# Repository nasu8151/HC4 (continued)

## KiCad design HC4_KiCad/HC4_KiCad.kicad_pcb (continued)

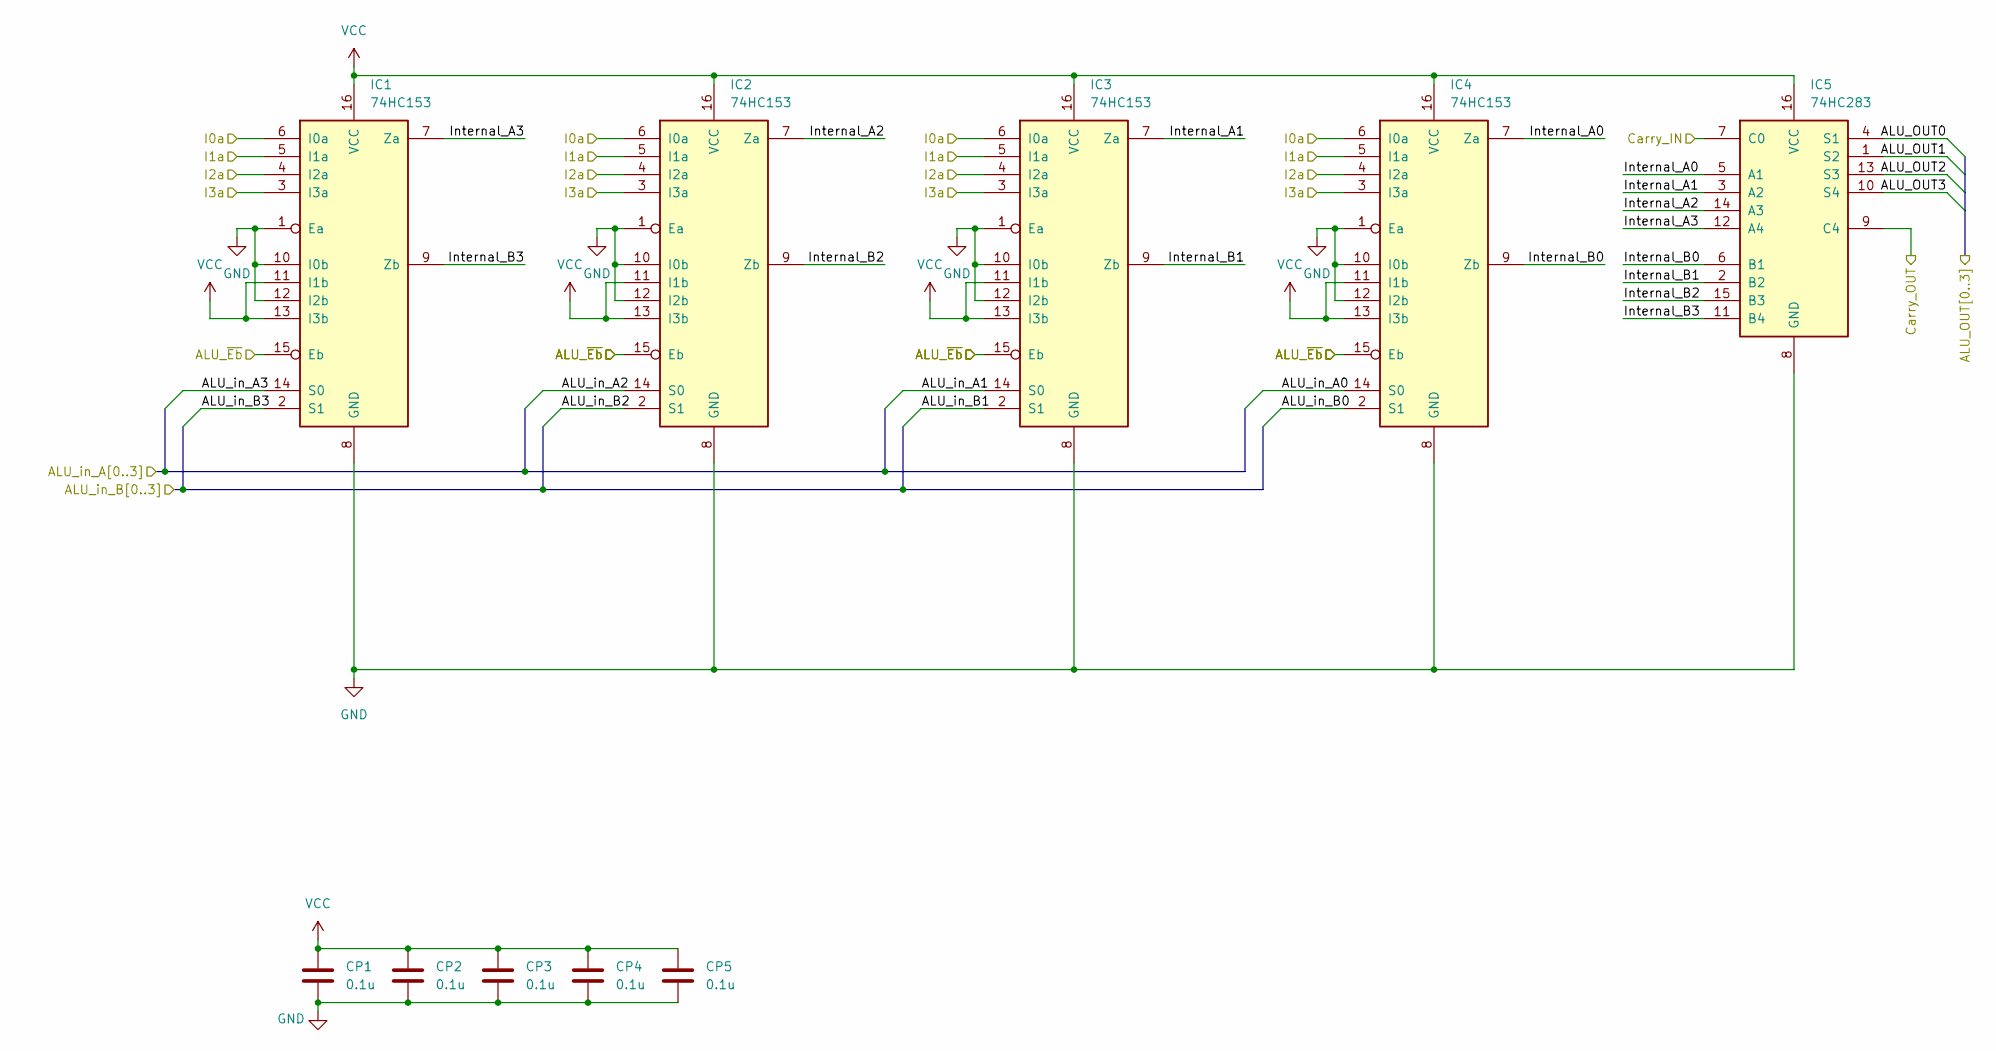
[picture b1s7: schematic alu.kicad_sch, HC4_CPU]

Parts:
CP1, CP2, CP3, CP4, CP5: 0.1u; C_0603_1608Metric
IC1, IC2, IC3, IC4: 74HC153; DIP-16_W7.62mm
IC5: 74HC283; DIP-16_W7.62mm

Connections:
/ALU/ALU_OUT0: IC5.4 (S1); also elsewhere on the board
/ALU/ALU_OUT1: IC5.1 (S2); also elsewhere on the board
/ALU/ALU_OUT2: IC5.13 (S3); also elsewhere on the board
/ALU/ALU_OUT3: IC5.10 (S4); also elsewhere on the board
/ALU/ALU_in_A0: IC4.14 (S0); also elsewhere on the board
/ALU/ALU_in_A1: IC3.14 (S0); also elsewhere on the board
/ALU/ALU_in_A2: IC2.14 (S0); also elsewhere on the board
/ALU/ALU_in_A3: IC1.14 (S0); also elsewhere on the board
/ALU/ALU_in_B0: IC4.2 (S1); also elsewhere on the board
/ALU/ALU_in_B1: IC3.2 (S1); also elsewhere on the board
/ALU/ALU_in_B2: IC2.2 (S1); also elsewhere on the board
/ALU/ALU_in_B3: IC1.2 (S1); also elsewhere on the board
/ALU/Carry_IN: IC1.6 (I0a), IC2.6 (I0a), IC3.6 (I0a), IC4.6 (I0a), IC5.7 (C0); also elsewhere on the board
/ALU/Carry_OUT: IC5.9 (C4); also elsewhere on the board
/ALU/I1a: IC1.5 (I1a), IC2.5 (I1a), IC3.5 (I1a), IC4.5 (I1a); also elsewhere on the board
/ALU/I2a: IC1.4 (I2a), IC2.4 (I2a), IC3.4 (I2a), IC4.4 (I2a); also elsewhere on the board
/ALU/I3a: IC1.3 (I3a), IC2.3 (I3a), IC3.3 (I3a), IC4.3 (I3a); also elsewhere on the board
/ALU/Internal_A0: IC4.7 (Za), IC5.5 (A1)
/ALU/Internal_A1: IC3.7 (Za), IC5.3 (A2)
/ALU/Internal_A2: IC2.7 (Za), IC5.14 (A3)
/ALU/Internal_A3: IC1.7 (Za), IC5.12 (A4)
/ALU/Internal_B0: IC4.9 (Zb), IC5.6 (B1)
/ALU/Internal_B1: IC3.9 (Zb), IC5.2 (B2)
/ALU/Internal_B2: IC2.9 (Zb), IC5.15 (B3)
/ALU/Internal_B3: IC1.9 (Zb), IC5.11 (B4)
/Instruction Decoder/~Carry_EN: IC1.15 (Eb), IC2.15 (Eb), IC3.15 (Eb), IC4.15 (Eb); also elsewhere on the board
GND: CP1.2, CP2.2, CP3.2, CP4.2, CP5.2, IC1.1 (Ea), IC1.8 (GND), IC1.10 (I0b), IC1.12 (I2b), IC2.1 (Ea), IC2.8 (GND), IC2.10 (I0b), IC2.12 (I2b), IC3.1 (Ea), IC3.8 (GND), IC3.10 (I0b), IC3.12 (I2b), IC4.1 (Ea), IC4.8 (GND), IC4.10 (I0b), IC4.12 (I2b), IC5.8 (GND); also elsewhere on the board
VCC: CP1.1, CP2.1, CP3.1, CP4.1, CP5.1, IC1.11 (I1b), IC1.13 (I3b), IC1.16 (VCC), IC2.11 (I1b), IC2.13 (I3b), IC2.16 (VCC), IC3.11 (I1b), IC3.13 (I3b), IC3.16 (VCC), IC4.11 (I1b), IC4.13 (I3b), IC4.16 (VCC), IC5.16 (VCC); also elsewhere on the board

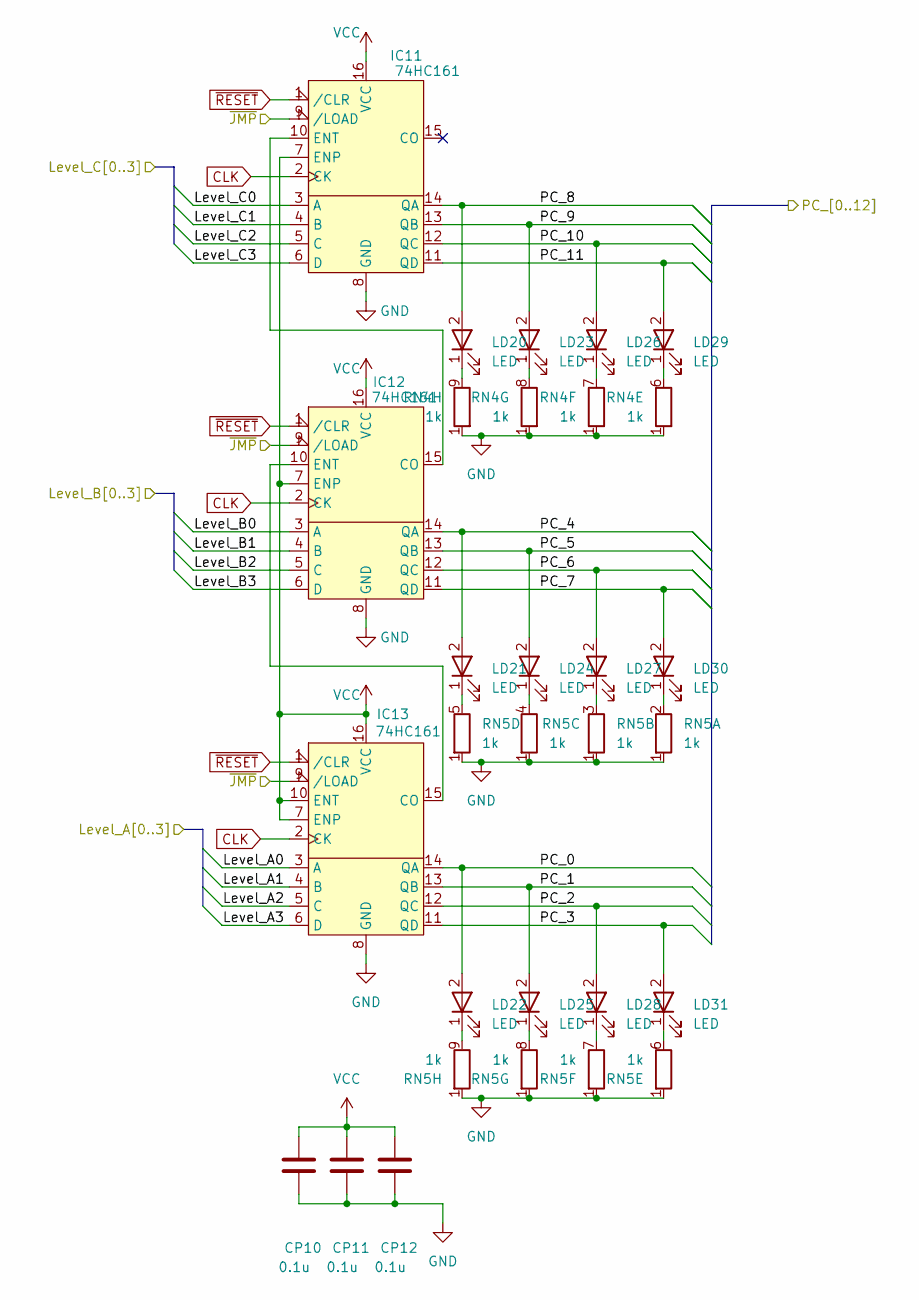
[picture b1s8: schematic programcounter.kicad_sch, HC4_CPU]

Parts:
CP10, CP11, CP12: 0.1u; C_0603_1608Metric
IC11, IC12, IC13: 74HC161; DIP-16_W7.62mm
LD20, LD21, LD22, LD23, LD24, LD25, LD26, LD27, LD28, LD29, LD30, LD31: LED; LED_Rectangular_W5.0mm_H2.0mm
RN4, RN5: 1k; R_Array_SIP9

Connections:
/ALU/ALU_in_A0: IC13.3 (A); also elsewhere on the board
/ALU/ALU_in_A1: IC13.4 (B); also elsewhere on the board
/ALU/ALU_in_A2: IC13.5 (C); also elsewhere on the board
/ALU/ALU_in_A3: IC13.6 (D); also elsewhere on the board
/ALU/ALU_in_B0: IC12.3 (A); also elsewhere on the board
/ALU/ALU_in_B1: IC12.4 (B); also elsewhere on the board
/ALU/ALU_in_B2: IC12.5 (C); also elsewhere on the board
/ALU/ALU_in_B3: IC12.6 (D); also elsewhere on the board
/Data BUS/Level_C0: IC11.3 (A); also elsewhere on the board
/Data BUS/Level_C1: IC11.4 (B); also elsewhere on the board
/Data BUS/Level_C2: IC11.5 (C); also elsewhere on the board
/Data BUS/Level_C3: IC11.6 (D); also elsewhere on the board
/Instruction Decoder/~JMP: IC11.9 (/LOAD), IC12.9 (/LOAD), IC13.9 (/LOAD); also elsewhere on the board
/Program Counter/PC_0: IC13.14 (QA), LD22.2; also elsewhere on the board
/Program Counter/PC_1: IC13.13 (QB), LD25.2; also elsewhere on the board
/Program Counter/PC_2: IC13.12 (QC), LD28.2; also elsewhere on the board
/Program Counter/PC_3: IC13.11 (QD), LD31.2; also elsewhere on the board
/Program Counter/PC_4: IC12.14 (QA), LD21.2; also elsewhere on the board
/Program Counter/PC_5: IC12.13 (QB), LD24.2; also elsewhere on the board
/Program Counter/PC_6: IC12.12 (QC), LD27.2; also elsewhere on the board
/Program Counter/PC_7: IC12.11 (QD), LD30.2; also elsewhere on the board
/Program Counter/PC_8: IC11.14 (QA), LD20.2; also elsewhere on the board
/Program Counter/PC_9: IC11.13 (QB), LD23.2; also elsewhere on the board
/Program Counter/PC_10: IC11.12 (QC), LD26.2; also elsewhere on the board
/Program Counter/PC_11: IC11.11 (QD), LD29.2; also elsewhere on the board
CLK: IC11.2 (CK), IC12.2 (CK), IC13.2 (CK); also elsewhere on the board
GND: CP10.2, CP11.2, CP12.2, IC11.8 (GND), IC12.8 (GND), IC13.8 (GND), RN4.1 (R1), RN5.1 (R1); also elsewhere on the board
unnamed: IC11.10 (ENT), IC12.15 (CO)
unnamed: IC12.10 (ENT), IC13.15 (CO)
unnamed: LD20.1 (K_1), RN4.9 (R8.2)
unnamed: LD21.1 (K_1), RN5.5 (R4.2)
unnamed: LD22.1 (K_1), RN5.9 (R8.2)
unnamed: LD23.1 (K_1), RN4.8 (R7.2)
unnamed: LD24.1 (K_1), RN5.4 (R3.2)
unnamed: LD25.1 (K_1), RN5.8 (R7.2)
unnamed: LD26.1 (K_1), RN4.7 (R6.2)
unnamed: LD27.1 (K_1), RN5.3 (R2.2)
unnamed: LD28.1 (K_1), RN5.7 (R6.2)
unnamed: LD29.1 (K_1), RN4.6 (R5.2)
unnamed: LD30.1 (K_1), RN5.2 (R1.2)
unnamed: LD31.1 (K_1), RN5.6 (R5.2)
VCC: CP10.1, CP11.1, CP12.1, IC11.7 (ENP), IC11.16 (VCC), IC12.7 (ENP), IC12.16 (VCC), IC13.7 (ENP), IC13.10 (ENT), IC13.16 (VCC); also elsewhere on the board
~RESET: IC11.1 (/CLR), IC12.1 (/CLR), IC13.1 (/CLR); also elsewhere on the board

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
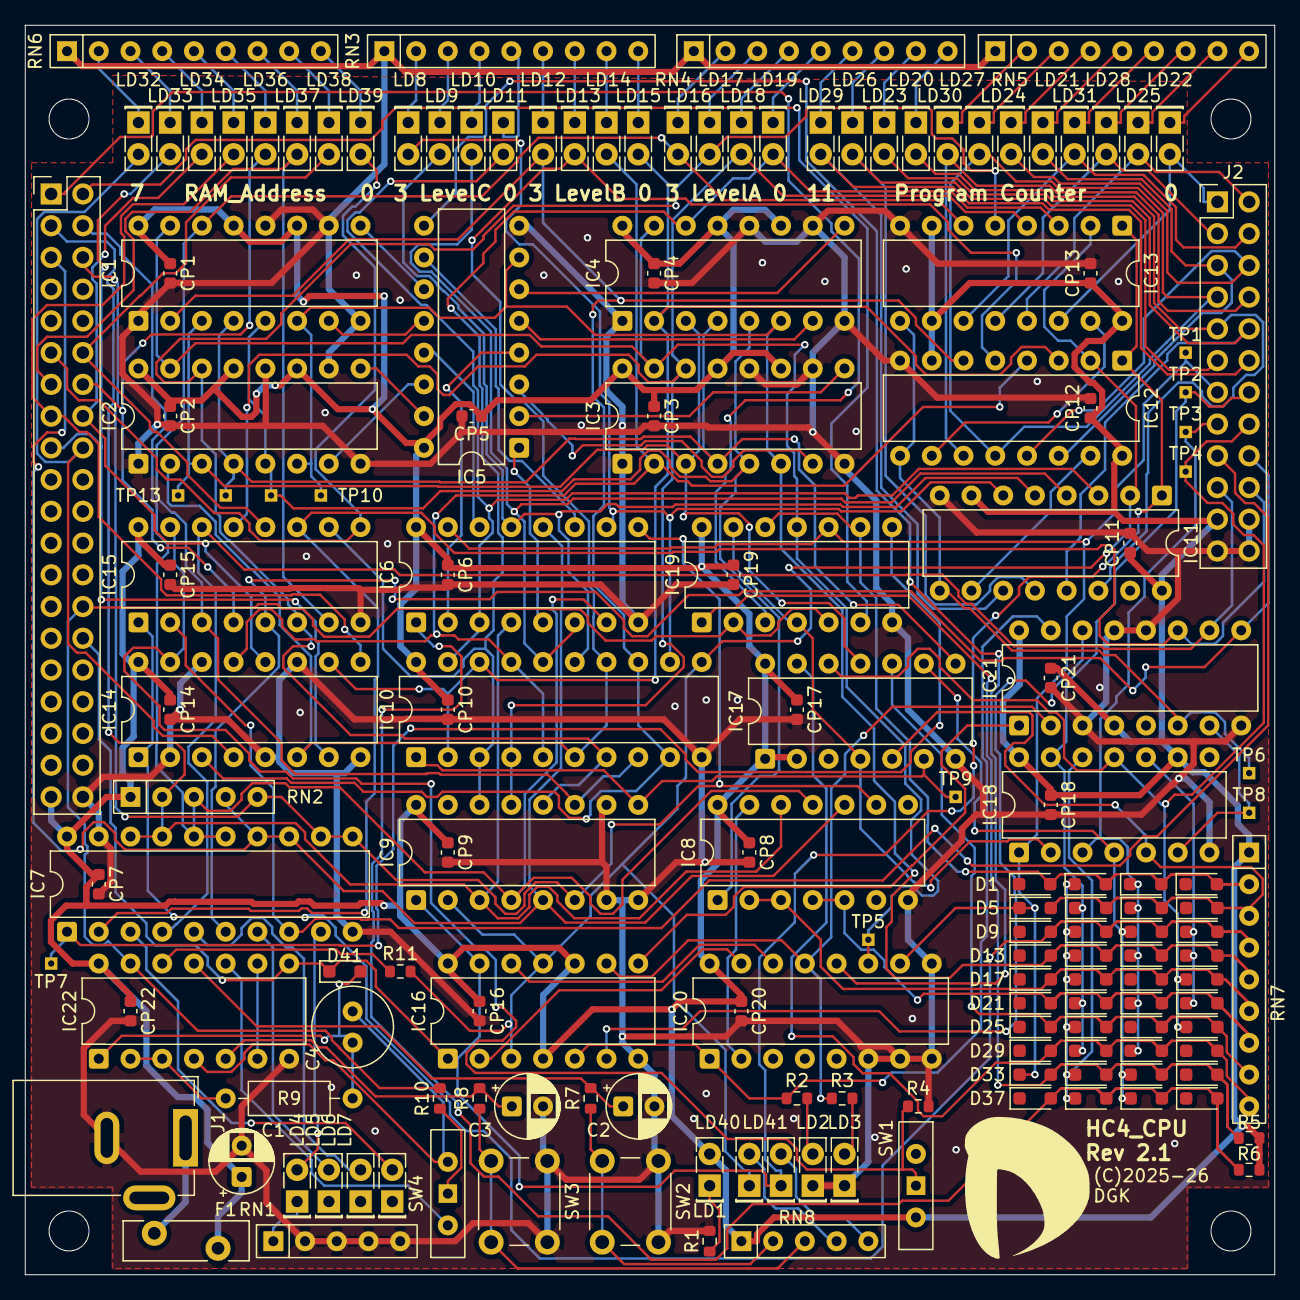
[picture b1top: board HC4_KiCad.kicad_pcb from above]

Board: 2 copper layers, 100.0 x 100.0 mm, 174 parts (0 on the bottom side), 150 nets.

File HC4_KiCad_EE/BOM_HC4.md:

| Value                       | Qty | Remarks                              |
| --------------------------- | --- | ------------------------------------ |
| Capacitor: 100u             | 1   |                                      |
| Capacitor: 10u              | 2   |                                      |
| Capacitor: 10u(Socket)      | 1   | Unipolar                             |
| Capacitor: 0.1u             | 24  |                                      |
| Zener: 5.6V                 | 1   |                                      |
| Diode: (1N4148 or equiv.)   | 40  |                                      |
| Polyfuse: 500mA             | 1   | For circuit protection               |
| RAM: (2716 ~ 27256)         | 1   |                                      |
| ROM: (6116~62256 or equiv.) | 1   | Write data hold time(tHD, tWHDX)=0ns |
| IC: 74HC153                 | 4   |                                      |
| IC: 74HC283                 | 1   |                                      |
| IC: 74HC257                 | 3   |                                      |
| IC: 74HC244                 | 1   |                                      |
| IC: 74HC4002                | 1   |                                      |
| IC: 74HC161                 | 4   |                                      |
| IC: 74HC377                 | 1   |                                      |
| IC: 74HC00                  | 1   |                                      |
| IC: 74HC32                  | 1   |                                      |
| IC: 74HC74                  | 1   |                                      |
| IC: 74HC4053                | 1   |                                      |
| IC: 74HC04                  | 1   |                                      |
| IC: 74HC151                 | 1   |                                      |
| IC: 74HC14                  | 1   |                                      |
| DC Jack                     | 1   |                                      |
| Pinheader: 01x01            | 1   |                                      |
| Pinheader: 02x20            | 1   |                                      |
| LED: 5mm                    | 1   |                                      |
| LED: Rectangle 2x3x4        | 26  |                                      |
| Resister: 1k                | 5   |                                      |
| Resister: 10k               | 4   |                                      |
| Resister: 100k              | 1   |                                      |
| Resister: 33k               | 1   |                                      |
| Resister: 100               | 2   |                                      |
| Resister array: 10k SIP5    | 1   |                                      |
| Resister array: 1k SIP5     | 3   |                                      |
| Resister array: 1k SIP9     | 3   |                                      |
| Resister array: 10k SIP9    | 1   |                                      |
| Slide SW_SPDT               | 3   |                                      |
| SW_Push                     | 2   |                                      |

[!Note]
* Please do not use mysterious Chinese parts.

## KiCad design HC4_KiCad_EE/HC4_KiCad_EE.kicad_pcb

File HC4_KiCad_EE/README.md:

Schematics and board of HC4<sub>E</sub> (E means "for Education").

BOM:
[Bill of materials](https://github.com/nasu8151/HC4/blob/main/HC4_KiCad/BOM_HC4.md)

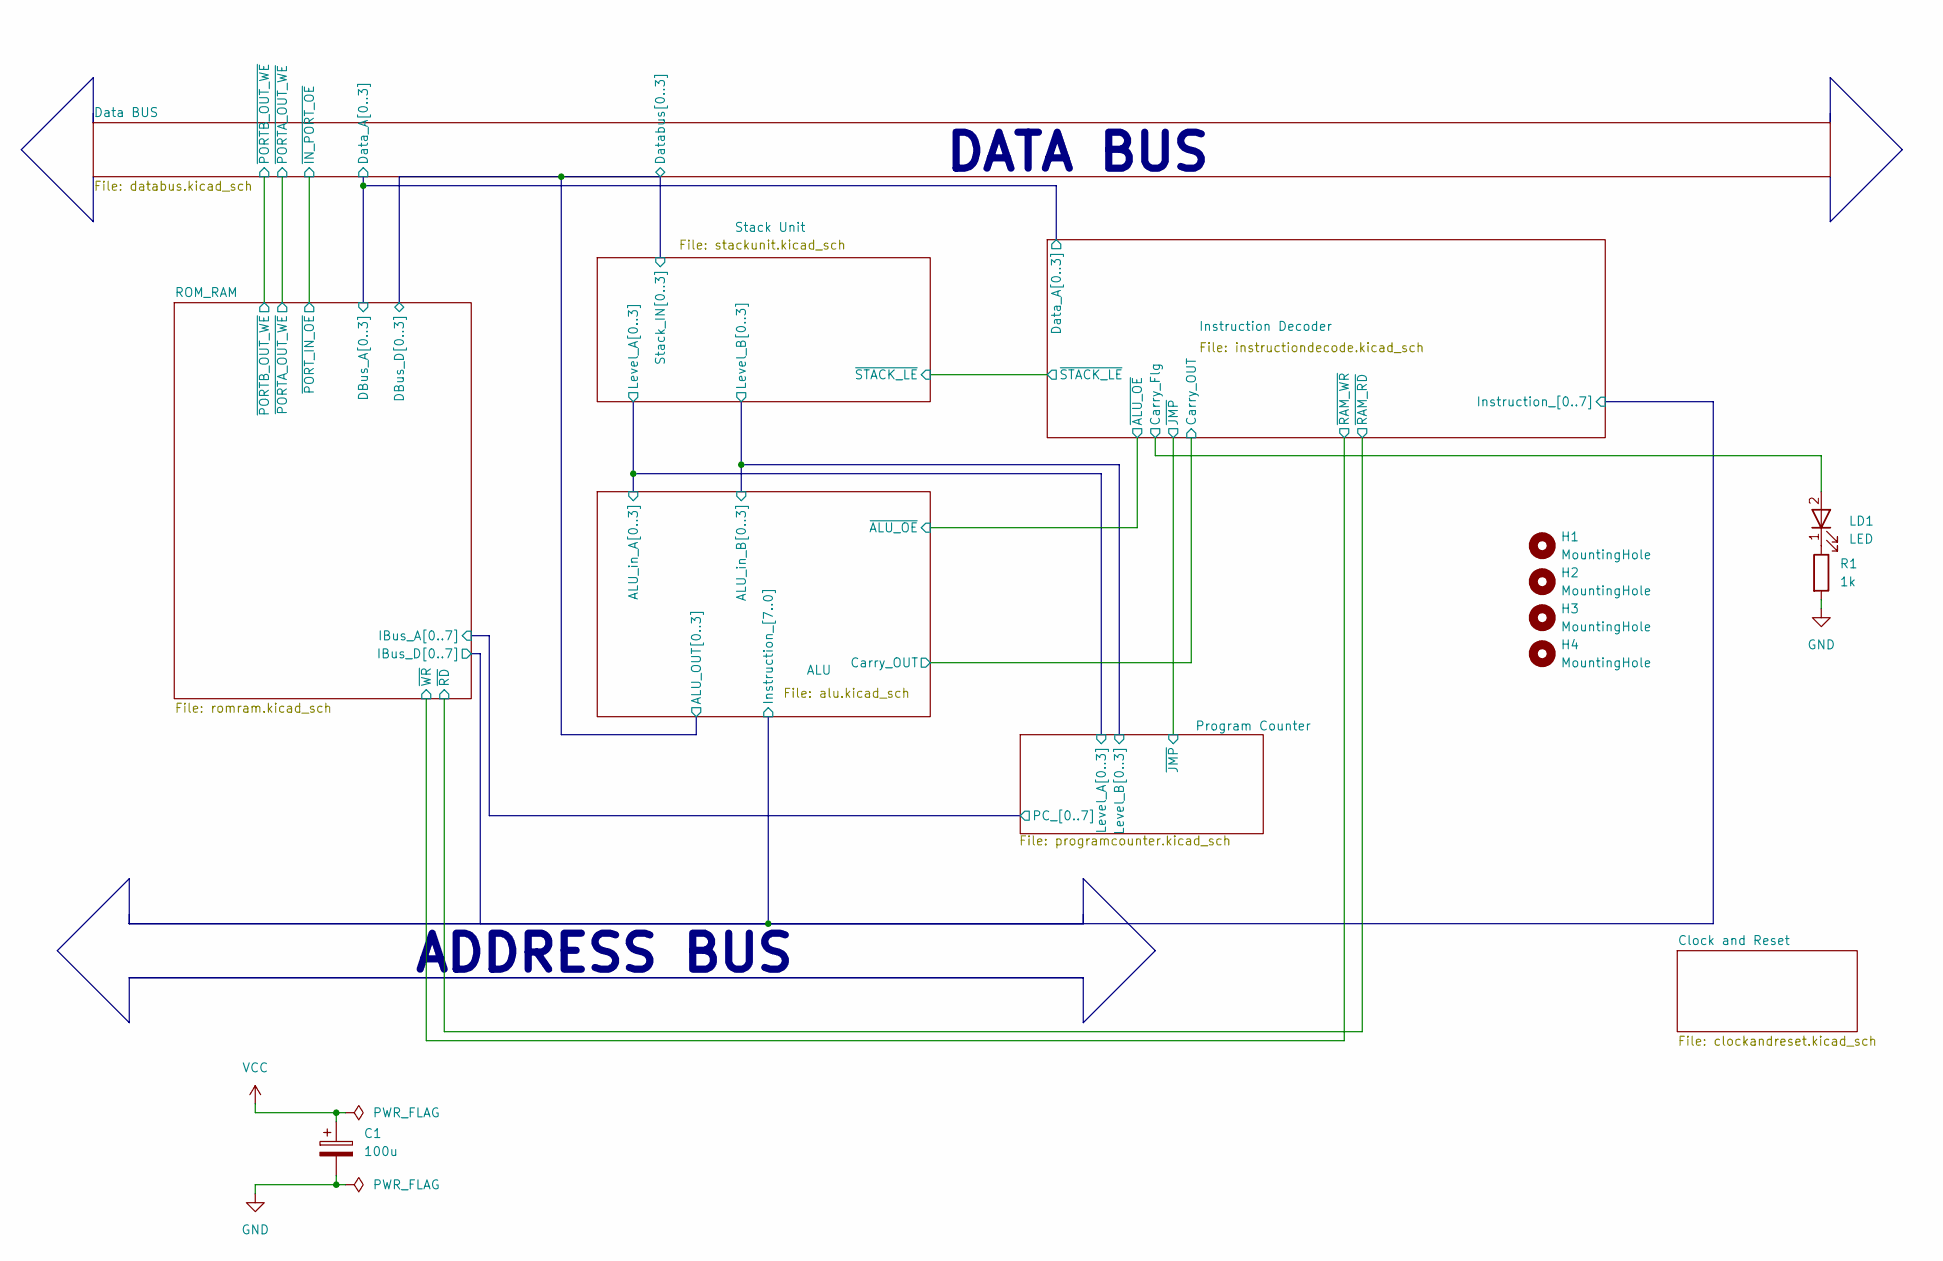
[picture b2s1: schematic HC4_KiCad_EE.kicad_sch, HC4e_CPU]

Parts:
C1: 100u; CP_Radial_D5.0mm_P2.50mm
H1, H2, H3, H4: MountingHole; MountingHole_3.2mm_M3
LD1: LED; LED_Rectangular_W5.0mm_H2.0mm
R1: 1k; R_0603_1608Metric; LCSC PN C21190

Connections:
/Instruction Decoder/Carry_Flg: LD1.2; also elsewhere on the board
GND: C1.2, R1.2; also elsewhere on the board
unnamed: LD1.1 (K_1), R1.1
VCC: C1.1; also elsewhere on the board

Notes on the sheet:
ADDRESS BUS
DATA BUS

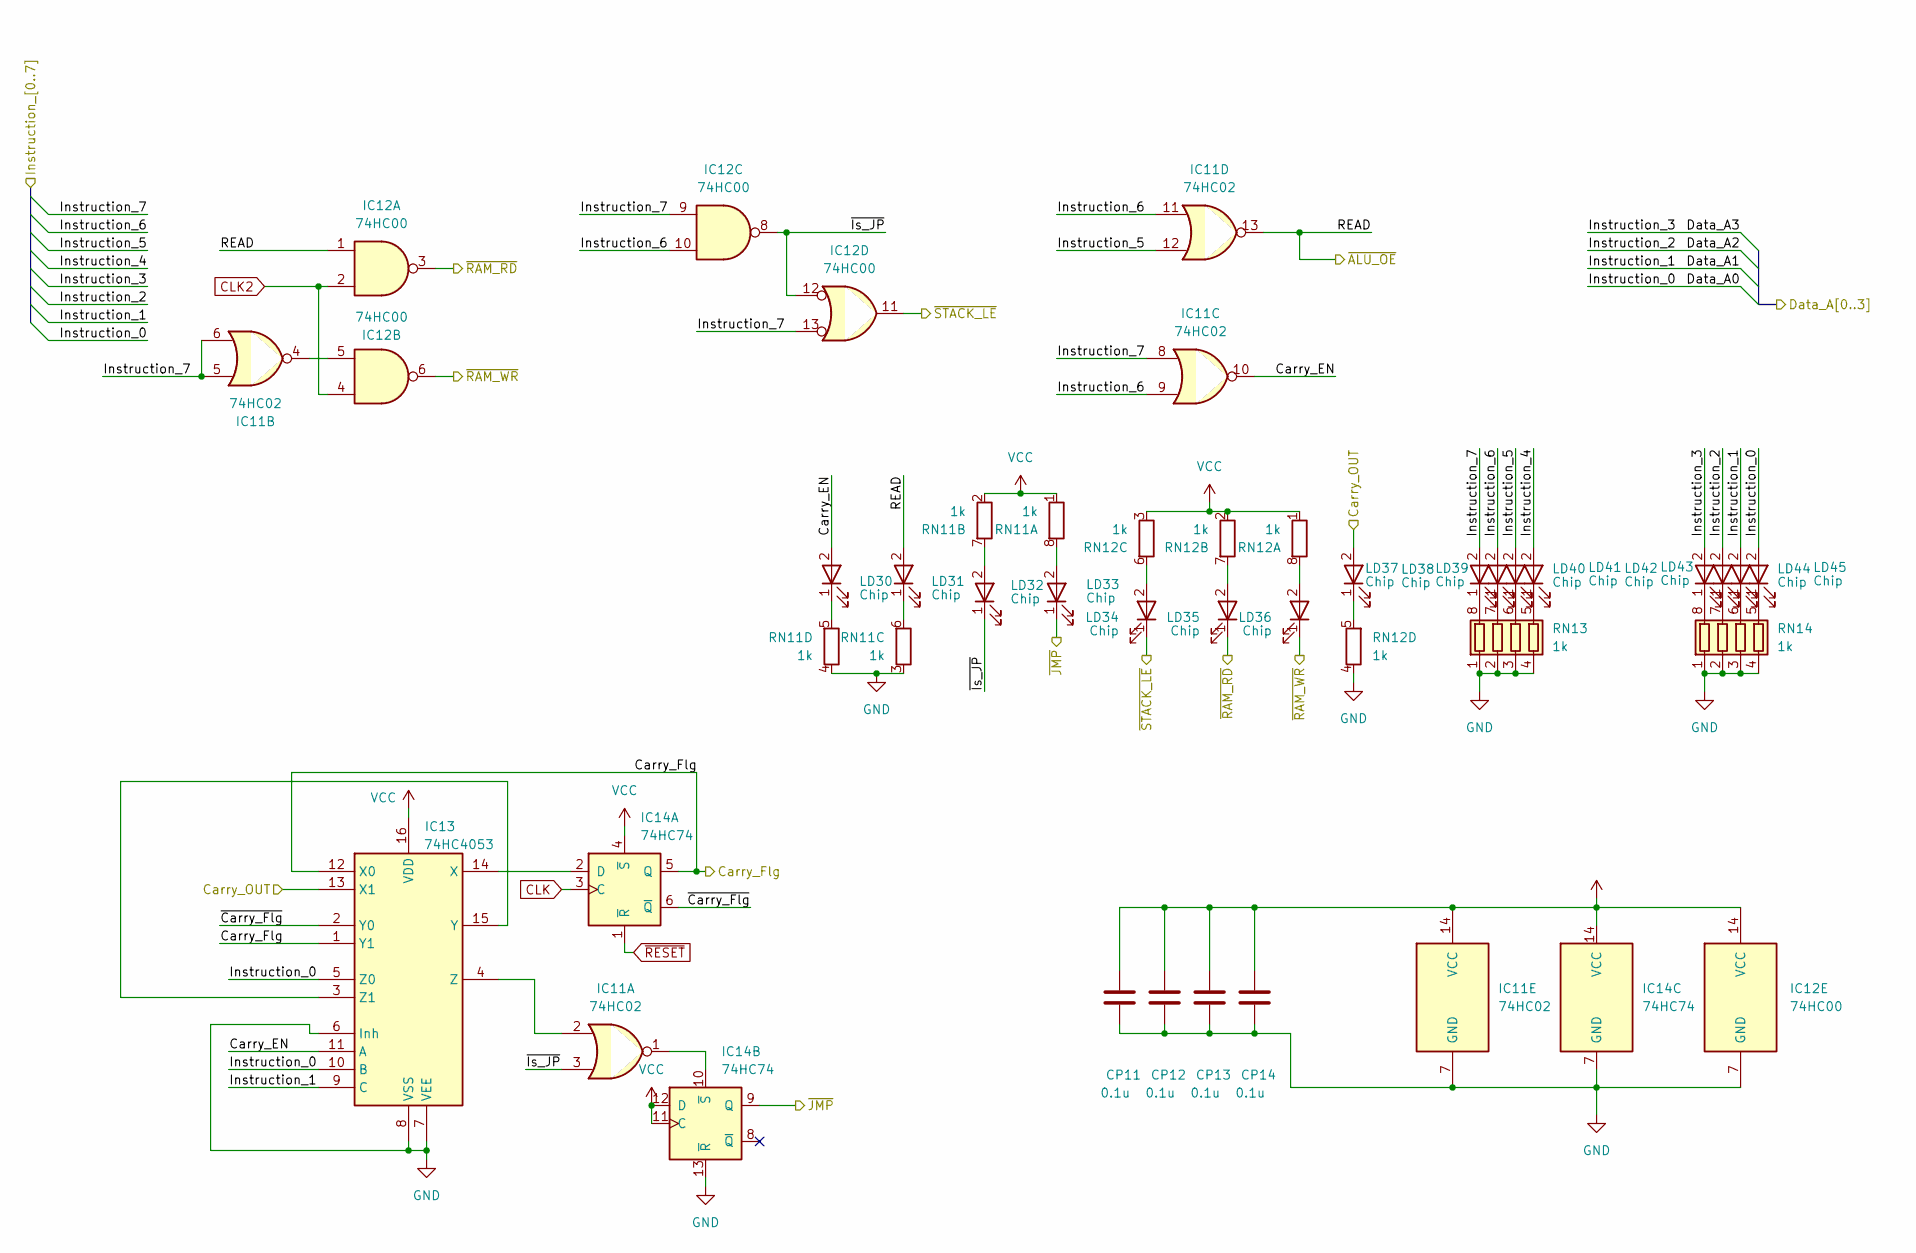
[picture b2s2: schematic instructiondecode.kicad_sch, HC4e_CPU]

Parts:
CP11, CP12, CP13, CP14: 0.1u; C_0603_1608Metric; LCSC PN C14663
IC11: 74HC02; SO-14_5.3x10.2mm_P1.27mm
IC12: 74HC00; SO-14_5.3x10.2mm_P1.27mm
IC13: 74HC4053; SO-16_5.3x10.2mm_P1.27mm
IC14: 74HC74; SO-14_5.3x10.2mm_P1.27mm
LD30, LD31, LD32, LD33, LD34, LD35, LD36, LD37, LD38, LD39, LD40, LD41, LD42, LD43, LD44, LD45: Chip; LED_0603_1608Metric; LCSC PN C2289
RN11, RN12, RN13, RN14: 1k; R_Array_Convex_4x0603; LCSC PN C20197

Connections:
/ALU/Carry_OUT: IC13.13 (X1), LD37.2; also elsewhere on the board
/ALU/Instruction_4: LD41.2; also elsewhere on the board
/ALU/Instruction_5: IC11.12, LD40.2; also elsewhere on the board
/ALU/Instruction_6: IC11.9, IC11.11, IC12.10, LD39.2; also elsewhere on the board
/ALU/Instruction_7: IC11.5, IC11.6, IC11.8, IC12.9, IC12.13, LD38.2; also elsewhere on the board
/Instruction Decoder/Carry_EN: IC11.10, IC13.11 (A), LD30.2
/Instruction Decoder/Carry_Flg: IC13.1 (Y1), IC13.12 (X0), IC14.5 (Q); also elsewhere on the board
/Instruction Decoder/READ: IC11.13, IC12.1, LD31.2; also elsewhere on the board
/Instruction Decoder/~Carry_Flg: IC13.2 (Y0), IC14.6 (~Q)
/Instruction Decoder/~Is_JP: IC11.3, IC12.8, IC12.12, LD32.1 (K_1)
/Instruction Decoder/~JMP: IC14.9 (Q), LD33.1 (K_1); also elsewhere on the board
/Instruction Decoder/~RAM_RD: IC12.3, LD35.1 (K_1); also elsewhere on the board
/Instruction Decoder/~RAM_WR: IC12.6, LD36.1 (K_1); also elsewhere on the board
/Instruction Decoder/~STACK_LE: IC12.11, LD34.1 (K_1); also elsewhere on the board
CLK: IC14.3 (C); also elsewhere on the board
CLK2: IC12.2, IC12.4; also elsewhere on the board
GND: CP11.2, CP12.2, CP13.2, CP14.2, IC11.7 (GND), IC12.7 (GND), IC13.6 (Inh), IC13.7 (VEE), IC13.8 (VSS), IC14.7 (GND), IC14.13 (~R), RN11.3 (R3.1), RN11.4 (R4.1), RN12.4 (R4.1), RN13.1 (R1.1), RN13.2 (R2.1), RN13.3 (R3.1), RN13.4 (R4.1), RN14.1 (R1.1), RN14.2 (R2.1), RN14.3 (R3.1), RN14.4 (R4.1); also elsewhere on the board
unnamed: IC11.4, IC12.5
unnamed: IC13.14 (X), IC14.2 (D)
unnamed: IC13.3 (Z1), IC13.15 (Y)
unnamed: IC11.2, IC13.4 (Z)
unnamed: IC11.1, IC14.10 (~S)
unnamed: LD30.1 (K_1), RN11.5 (R4.2)
unnamed: LD31.1 (K_1), RN11.6 (R3.2)
unnamed: LD37.1 (K_1), RN12.5 (R4.2)
unnamed: LD38.1 (K_1), RN13.8 (R1.2)
unnamed: LD39.1 (K_1), RN13.7 (R2.2)
unnamed: LD40.1 (K_1), RN13.6 (R3.2)
unnamed: LD41.1 (K_1), RN13.5 (R4.2)
unnamed: LD42.1 (K_1), RN14.8 (R1.2)
unnamed: LD43.1 (K_1), RN14.7 (R2.2)
unnamed: LD44.1 (K_1), RN14.6 (R3.2)
unnamed: LD45.1 (K_1), RN14.5 (R4.2)
unnamed: LD33.2, RN11.8 (R1.2)
unnamed: LD32.2, RN11.7 (R2.2)
unnamed: LD36.2, RN12.8 (R1.2)
unnamed: LD35.2, RN12.7 (R2.2)
unnamed: LD34.2, RN12.6 (R3.2)
VCC: CP11.1, CP12.1, CP13.1, CP14.1, IC11.14 (VCC), IC12.14 (VCC), IC13.16 (VDD), IC14.4 (~S), IC14.11 (C), IC14.12 (D), IC14.14 (VCC), RN11.1 (R1.1), RN11.2 (R2.1), RN12.1 (R1.1), RN12.2 (R2.1), RN12.3 (R3.1); also elsewhere on the board
~RESET: IC14.1 (~R); also elsewhere on the board

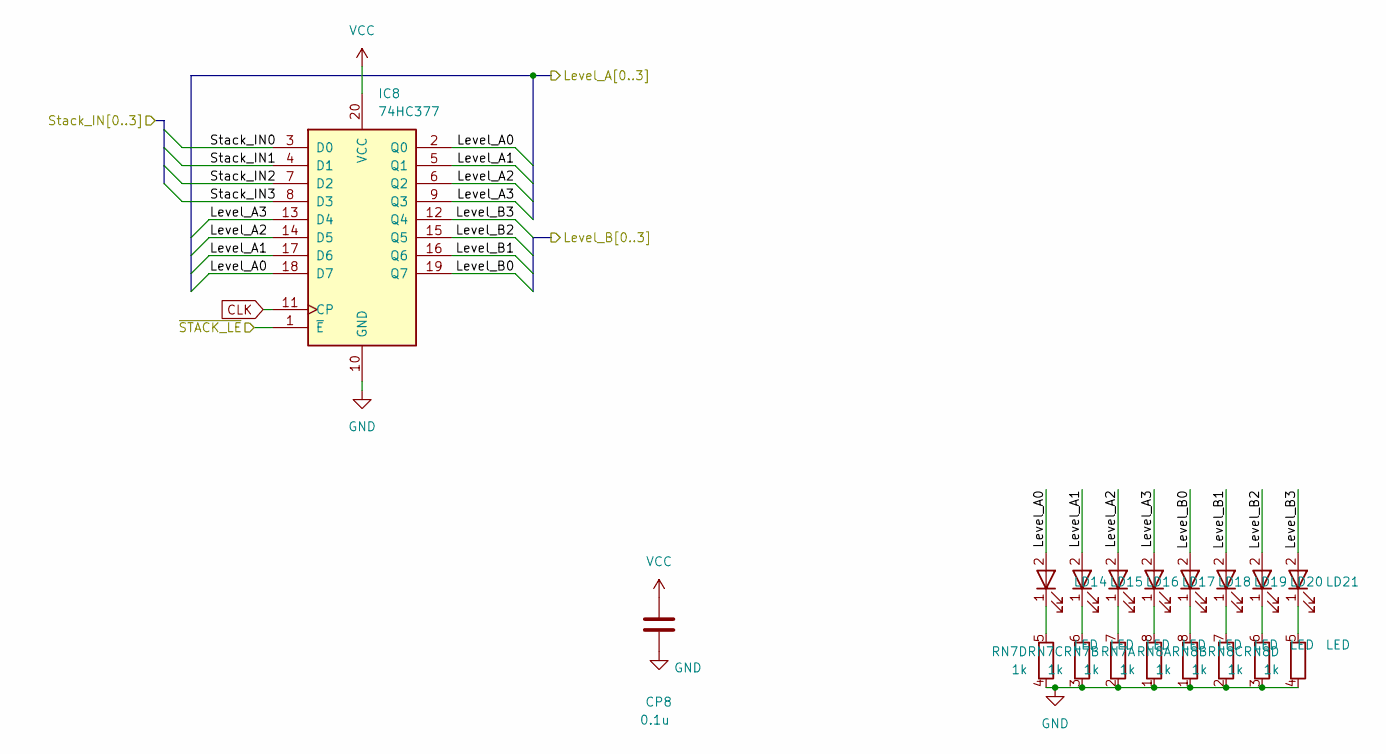
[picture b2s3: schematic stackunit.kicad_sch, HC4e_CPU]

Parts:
CP8: 0.1u; C_0603_1608Metric; LCSC PN C14663
IC8: 74HC377; SOIC-20W_7.5x12.8mm_P1.27mm
LD14, LD15, LD16, LD17, LD18, LD19, LD20, LD21: LED; LED_Rectangular_W5.0mm_H2.0mm
RN7, RN8: 1k; R_Array_Convex_4x0603; LCSC PN C20197

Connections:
/ALU/ALU_OUT0: IC8.3 (D0); also elsewhere on the board
/ALU/ALU_OUT1: IC8.4 (D1); also elsewhere on the board
/ALU/ALU_OUT2: IC8.7 (D2); also elsewhere on the board
/ALU/ALU_OUT3: IC8.8 (D3); also elsewhere on the board
/ALU/ALU_in_A0: IC8.2 (Q0), IC8.18 (D7), LD14.2; also elsewhere on the board
/ALU/ALU_in_A1: IC8.5 (Q1), IC8.17 (D6), LD15.2; also elsewhere on the board
/ALU/ALU_in_A2: IC8.6 (Q2), IC8.14 (D5), LD16.2; also elsewhere on the board
/ALU/ALU_in_A3: IC8.9 (Q3), IC8.13 (D4), LD17.2; also elsewhere on the board
/ALU/ALU_in_B0: IC8.19 (Q7), LD18.2; also elsewhere on the board
/ALU/ALU_in_B1: IC8.16 (Q6), LD19.2; also elsewhere on the board
/ALU/ALU_in_B2: IC8.15 (Q5), LD20.2; also elsewhere on the board
/ALU/ALU_in_B3: IC8.12 (Q4), LD21.2; also elsewhere on the board
/Instruction Decoder/~STACK_LE: IC8.1 (~E); also elsewhere on the board
CLK: IC8.11 (CP); also elsewhere on the board
GND: CP8.2, IC8.10 (GND), RN7.1 (R1.1), RN7.2 (R2.1), RN7.3 (R3.1), RN7.4 (R4.1), RN8.1 (R1.1), RN8.2 (R2.1), RN8.3 (R3.1), RN8.4 (R4.1); also elsewhere on the board
unnamed: LD14.1 (K_1), RN7.5 (R4.2)
unnamed: LD15.1 (K_1), RN7.6 (R3.2)
unnamed: LD16.1 (K_1), RN7.7 (R2.2)
unnamed: LD17.1 (K_1), RN7.8 (R1.2)
unnamed: LD18.1 (K_1), RN8.8 (R1.2)
unnamed: LD19.1 (K_1), RN8.7 (R2.2)
unnamed: LD20.1 (K_1), RN8.6 (R3.2)
unnamed: LD21.1 (K_1), RN8.5 (R4.2)
VCC: CP8.1, IC8.20 (VCC); also elsewhere on the board

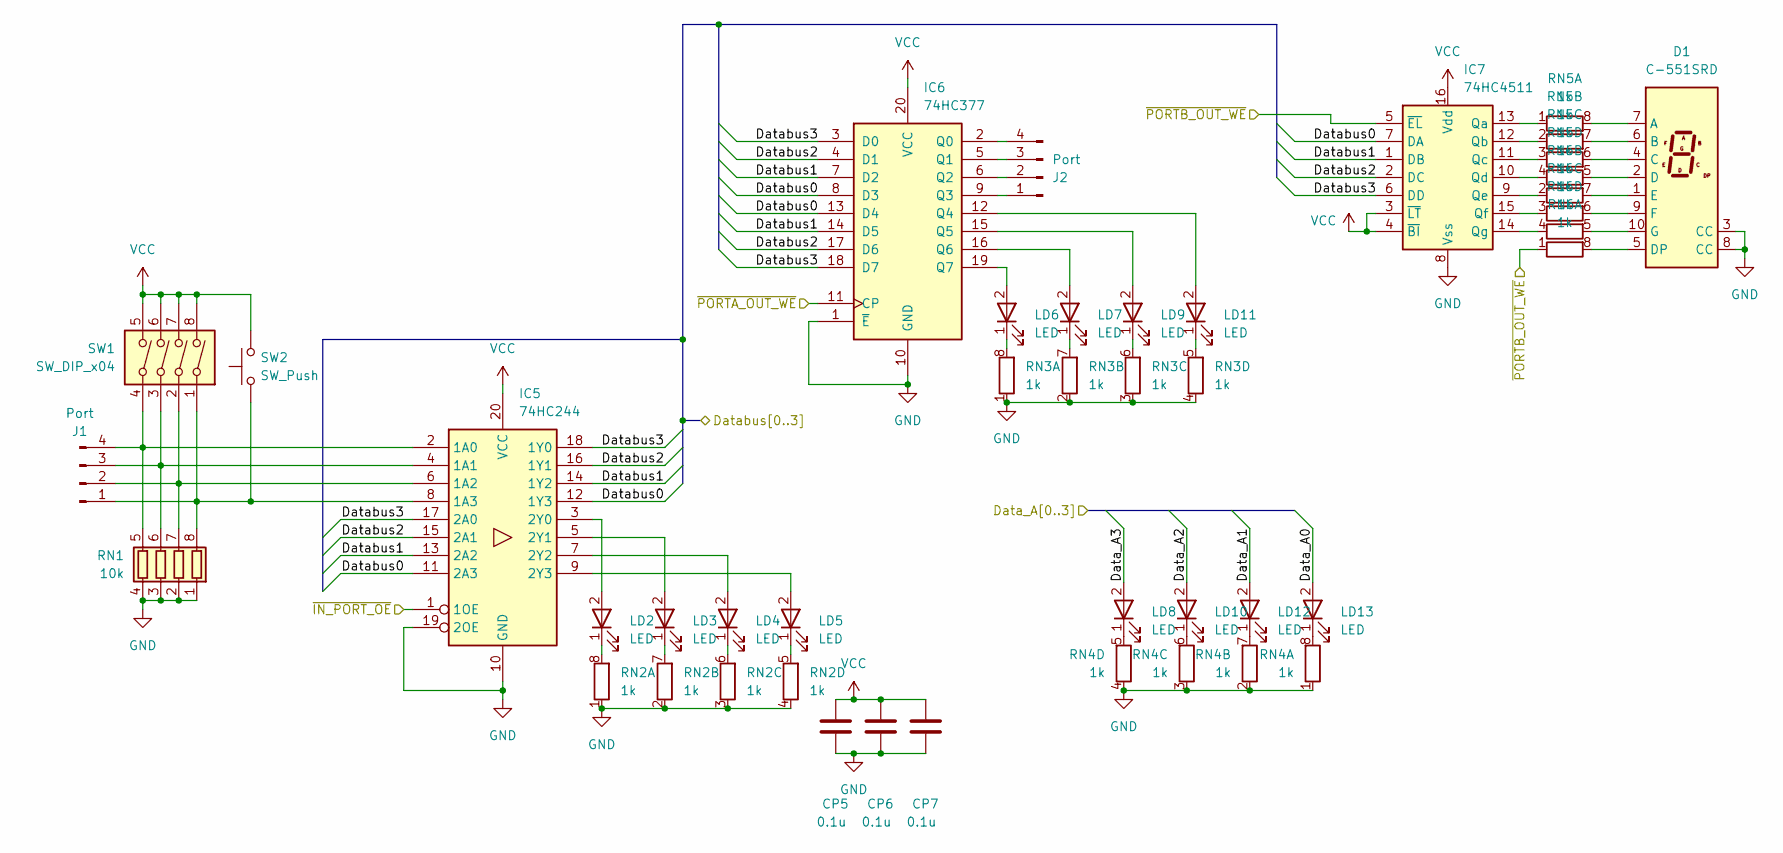
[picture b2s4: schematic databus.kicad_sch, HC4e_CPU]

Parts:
CP5, CP6, CP7: 0.1u; C_0603_1608Metric; LCSC PN C14663
D1: C-551SRD; D1X8K
IC5: 74HC244; SOIC-20W_7.5x12.8mm_P1.27mm
IC6: 74HC377; SOIC-20W_7.5x12.8mm_P1.27mm
IC7: 74HC4511; SO-16_5.3x10.2mm_P1.27mm
J1, J2: Port; PinHeader_1x04_P2.54mm_Vertical
LD2, LD3, LD4, LD5, LD6, LD7, LD8, LD9, LD10, LD11, LD12, LD13: LED; LED_Rectangular_W5.0mm_H2.0mm
RN1: 10k; R_Array_Convex_4x0603; LCSC PN C29718
RN2, RN3, RN4, RN5, RN6: 1k; R_Array_Convex_4x0603; LCSC PN C20197
SW1: SW_DIP_x04; SW_DIP_SPSTx04_Slide_9.78x12.34mm_W7.62mm_P2.54mm
SW2: SW_Push; SW_PUSH_6mm

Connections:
/ALU/ALU_OUT0: IC5.11 (2A3), IC5.12 (1Y3), IC6.8 (D3), IC6.13 (D4), IC7.7 (DA); also elsewhere on the board
/ALU/ALU_OUT1: IC5.13 (2A2), IC5.14 (1Y2), IC6.7 (D2), IC6.14 (D5), IC7.1 (DB); also elsewhere on the board
/ALU/ALU_OUT2: IC5.15 (2A1), IC5.16 (1Y1), IC6.4 (D1), IC6.17 (D6), IC7.2 (DC); also elsewhere on the board
/ALU/ALU_OUT3: IC5.17 (2A0), IC5.18 (1Y0), IC6.3 (D0), IC6.18 (D7), IC7.6 (DD); also elsewhere on the board
/Data BUS/~IN_PORT_OE: IC5.1 (1OE); also elsewhere on the board
/Data BUS/~PORTA_OUT_WE: IC6.11 (CP); also elsewhere on the board
/Data BUS/~PORTB_OUT_WE: IC7.5 (~EL), RN6.1 (R1.1); also elsewhere on the board
GND: CP5.2, CP6.2, CP7.2, D1.3 (CC), D1.8 (CC), IC5.10 (GND), IC5.19 (2OE), IC6.1 (~E), IC6.10 (GND), IC7.8 (Vss), RN1.1 (R1.1), RN1.2 (R2.1), RN1.3 (R3.1), RN1.4 (R4.1), RN2.1 (R1.1), RN2.2 (R2.1), RN2.3 (R3.1), RN2.4 (R4.1), RN3.1 (R1.1), RN3.2 (R2.1), RN3.3 (R3.1), RN3.4 (R4.1), RN4.1 (R1.1), RN4.2 (R2.1), RN4.3 (R3.1), RN4.4 (R4.1); also elsewhere on the board
unnamed: D1.7 (A), RN5.8 (R1.2)
unnamed: D1.6 (B), RN5.7 (R2.2)
unnamed: D1.4 (C), RN5.6 (R3.2)
unnamed: D1.2 (D), RN5.5 (R4.2)
unnamed: D1.5 (DP), RN6.8 (R1.2)
unnamed: D1.1 (E), RN6.7 (R2.2)
unnamed: D1.9 (F), RN6.6 (R3.2)
unnamed: D1.10 (G), RN6.5 (R4.2)
unnamed: IC5.2 (1A0), J1.4, RN1.5 (R4.2), SW1.4
unnamed: IC5.4 (1A1), J1.3, RN1.6 (R3.2), SW1.3
unnamed: IC5.6 (1A2), J1.2, RN1.7 (R2.2), SW1.2
unnamed: IC5.8 (1A3), J1.1, RN1.8 (R1.2), SW1.1, SW2.1
unnamed: IC5.3 (2Y0), LD2.2
unnamed: IC5.5 (2Y1), LD3.2
unnamed: IC5.7 (2Y2), LD4.2
unnamed: IC5.9 (2Y3), LD5.2
unnamed: IC6.2 (Q0), J2.4
unnamed: IC6.5 (Q1), J2.3
unnamed: IC6.6 (Q2), J2.2
unnamed: IC6.9 (Q3), J2.1
unnamed: IC6.12 (Q4), LD11.2
unnamed: IC6.15 (Q5), LD9.2
unnamed: IC6.16 (Q6), LD7.2
unnamed: IC6.19 (Q7), LD6.2
unnamed: IC7.13 (Qa), RN5.1 (R1.1)
unnamed: IC7.12 (Qb), RN5.2 (R2.1)
unnamed: IC7.11 (Qc), RN5.3 (R3.1)
unnamed: IC7.10 (Qd), RN5.4 (R4.1)
unnamed: IC7.9 (Qe), RN6.2 (R2.1)
unnamed: IC7.15 (Qf), RN6.3 (R3.1)
unnamed: IC7.14 (Qg), RN6.4 (R4.1)
unnamed: LD2.1 (K_1), RN2.8 (R1.2)
unnamed: LD3.1 (K_1), RN2.7 (R2.2)
unnamed: LD4.1 (K_1), RN2.6 (R3.2)
unnamed: LD5.1 (K_1), RN2.5 (R4.2)
unnamed: LD6.1 (K_1), RN3.8 (R1.2)
unnamed: LD7.1 (K_1), RN3.7 (R2.2)
unnamed: LD8.1 (K_1), RN4.5 (R4.2)
unnamed: LD9.1 (K_1), RN3.6 (R3.2)
unnamed: LD10.1 (K_1), RN4.6 (R3.2)
unnamed: LD11.1 (K_1), RN3.5 (R4.2)
unnamed: LD12.1 (K_1), RN4.7 (R2.2)
unnamed: LD13.1 (K_1), RN4.8 (R1.2)
VCC: CP5.1, CP6.1, CP7.1, IC5.20 (VCC), IC6.20 (VCC), IC7.3 (~LT), IC7.4 (~BI), IC7.16 (Vdd), SW1.5, SW1.6, SW1.7, SW1.8, SW2.2; also elsewhere on the board
